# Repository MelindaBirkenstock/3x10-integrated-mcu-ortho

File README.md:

# 3x10 integrated mcu ortho
 title

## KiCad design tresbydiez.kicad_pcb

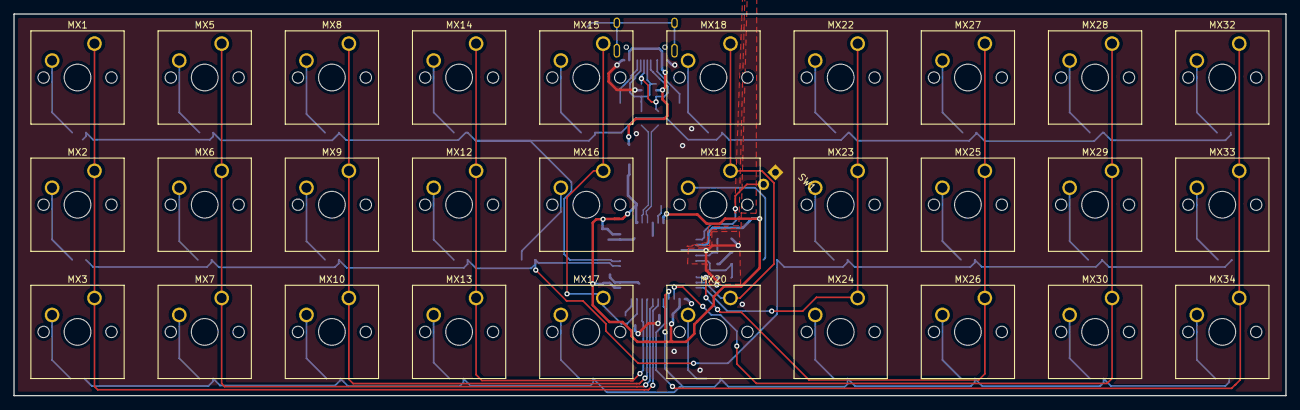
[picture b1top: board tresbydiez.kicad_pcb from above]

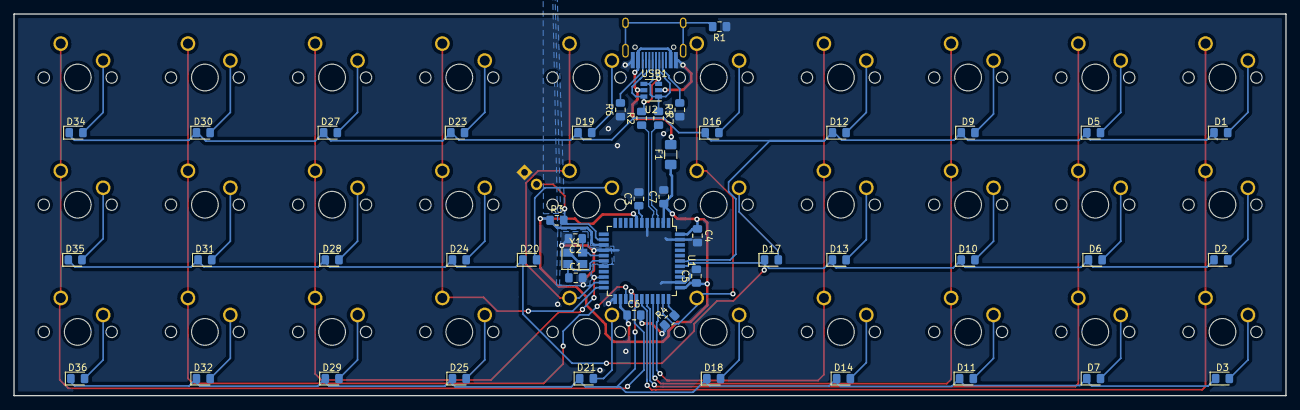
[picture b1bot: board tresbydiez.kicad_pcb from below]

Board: 2 copper layers, 190.5 x 57.1 mm, 80 parts (49 on the bottom side), 58 nets.

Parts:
C1, C2: 22pF; C_0805_2012Metric_Pad1.15x1.40mm_HandSolder
C3: 1uF; C_0805_2012Metric_Pad1.15x1.40mm_HandSolder
C4, C5, C6: 0.1uF; C_0805_2012Metric_Pad1.15x1.40mm_HandSolder
C7: 10uF; C_0805_2012Metric_Pad1.15x1.40mm_HandSolder
D1, D2, D3, D5, D6, D7, D9, D10, D11, D12, D13, D14, D16, D17, D18, D19, D20, D21, D23, D24, D25, D27, D28, D29, D30, D31, D32, D34, D35, D36: D; D_0805_2012Metric_Pad1.15x1.40mm_HandSolder
F1: 500mA; Fuse_1206_3216Metric_Pad1.42x1.75mm_HandSolder
MX1, MX2, MX3, MX5, MX6, MX7, MX8, MX9, MX10, MX12, MX13, MX14, MX15, MX16, MX17, MX18, MX19, MX20, MX22, MX23, MX24, MX25, MX26, MX27, MX28, MX29, MX30, MX32, MX33, MX34: MX-NoLED; SW_Cherry_MX_1.00u_PCB
R1: 1M; R_0805_2012Metric_Pad1.15x1.40mm_HandSolder
R2, R7: 22; R_0805_2012Metric_Pad1.15x1.40mm_HandSolder
R3, R4: 10k; R_0805_2012Metric_Pad1.15x1.40mm_HandSolder
R5, R6: 5.1k; R_0805_2012Metric_Pad1.15x1.40mm_HandSolder
SW1: SW_Push; PinHeader_1x02_P2.54mm_Horizontal
U1: ATmega32U4-AU; TQFP-44_10x10mm_P0.8mm
U2: SRV05-4; SOT-23-6
USB1: HRO-TYPE-C-31-M-12; HRO-TYPE-C-31-M-12-HandSoldering
Y1: 16MHz; Crystal_SMD_3225-4Pin_3.2x2.5mm

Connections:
+5V: C4.1, C5.1, C6.1, C7.1, F1.1, R3.1, U1.2, U1.7, U1.14, U1.24, U1.34, U1.44
COL0: MX1.1, MX2.1, MX3.1, U1.28
COL1: MX5.1, MX6.1, MX7.1, U1.29
COL2: MX8.1, MX9.1, MX10.1, U1.30
COL3: MX12.1, MX13.1, MX14.1, U1.31
COL4: MX15.1, MX16.1, MX17.1, U1.32
COL5: MX18.1, MX19.1, MX20.1, U1.21
COL6: MX22.1, MX23.1, MX24.1, U1.22
COL7: MX25.1, MX26.1, MX27.1, U1.20
COL8: MX28.1, MX29.1, MX30.1, U1.25
COL9: MX32.1, MX33.1, MX34.1, U1.27
D+: R2.1, U1.4
D-: R7.2, U1.3
DBUS+: R2.2, U2.3, U2.6, USB1.6, USB1.8
DBUS-: R7.1, U2.1, U2.4, USB1.5, USB1.7
GND: C1.2, C2.2, C3.2, C4.2, C5.2, C6.2, C7.2, R1.1, R4.1, R5.1, R6.1, SW1.1, U1.5, U1.15, U1.23, U1.35, U1.43, U2.2, USB1.1, USB1.12, Y1.2, Y1.4
GNDREF: R1.2, USB1.13
unnamed: C1.1, U1.17, Y1.1
unnamed: C2.1, U1.16, Y1.3
unnamed: C3.1, U1.6
unnamed: D1.2, MX1.2
unnamed: D2.2, MX2.2
unnamed: D3.2, MX3.2
unnamed: D5.2, MX5.2
unnamed: D6.2, MX6.2
unnamed: D7.2, MX7.2
unnamed: D9.2, MX8.2
unnamed: D10.2, MX9.2
unnamed: D11.2, MX10.2
unnamed: D12.2, MX14.2
unnamed: D13.2, MX12.2
unnamed: D14.2, MX13.2
unnamed: D16.2, MX15.2
unnamed: D17.2, MX16.2
unnamed: D18.2, MX17.2
unnamed: D19.2, MX18.2
unnamed: D20.2, MX19.2
unnamed: D21.2, MX20.2
unnamed: D23.2, MX22.2
unnamed: D24.2, MX23.2
unnamed: D25.2, MX24.2
unnamed: D27.2, MX27.2
unnamed: D28.2, MX25.2
unnamed: D29.2, MX26.2
unnamed: D30.2, MX28.2
unnamed: D31.2, MX29.2
unnamed: D32.2, MX30.2
unnamed: D34.2, MX32.2
unnamed: D35.2, MX33.2
unnamed: D36.2, MX34.2
unnamed: R3.2, SW1.2, U1.13
unnamed: R4.2, U1.33
unnamed: R5.2, USB1.4
unnamed: R6.2, USB1.10
ROW0: D1.1, D5.1, D9.1, D12.1, D16.1, D19.1, D23.1, D27.1, D30.1, D34.1, U1.39
ROW1: D2.1, D6.1, D10.1, D13.1, D17.1, D20.1, D24.1, D28.1, D31.1, D35.1, U1.38
ROW2: D3.1, D7.1, D11.1, D14.1, D18.1, D21.1, D25.1, D29.1, D32.1, D36.1, U1.26
VBUS: F1.2, U2.5, USB1.2, USB1.11

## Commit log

2020-07-22 First rev
    Its a 3x10 integrated mcu with ESD and USB-C, ain't much else to say.
